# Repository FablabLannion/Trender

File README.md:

# Trender
# Main SW used for Trender Project. See here for details: http://wiki.fablab-lannion.org/index.php?title=Trender

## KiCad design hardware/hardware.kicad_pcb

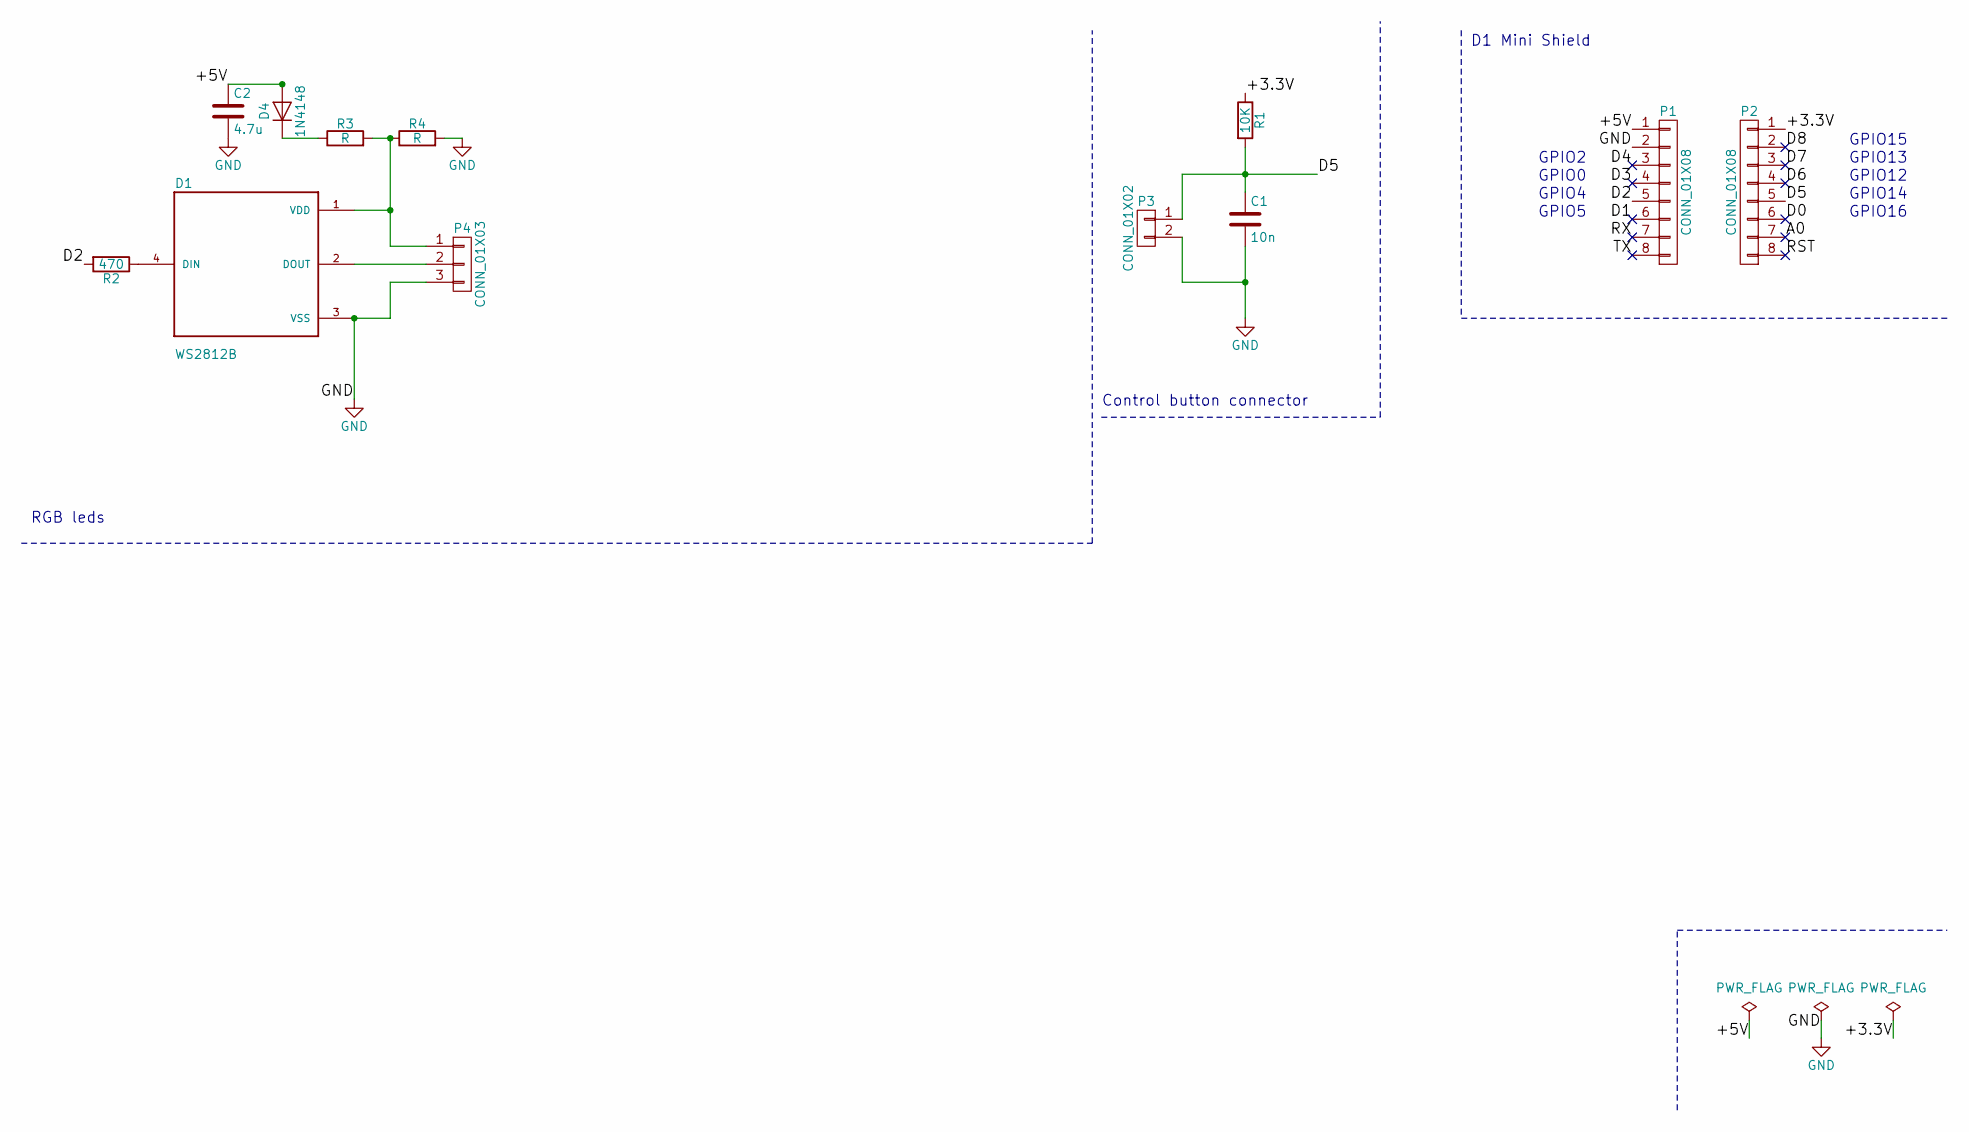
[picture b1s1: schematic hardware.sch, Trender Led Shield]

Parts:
C1: 10n; C_Disc_D3.8mm_W2.6mm_P2.50mm
C2: 4.7u; C_Disc_D3.8mm_W2.6mm_P2.50mm
D1: WS2812B; LED_WS2812B
D4: 1N4148; D_DO-15_P2.54mm_Vertical_KathodeUp
P1, P2: CONN_01X08; D1_mini_Pin_Header
P3: CONN_01X02; Pin_Header_Angled_1x02
P4: CONN_01X03; Pin_Header_Angled_1x03
R1: 10K; R_Axial_DIN0204_L3.6mm_D1.6mm_P2.54mm_Vertical
R2: 470; R_Axial_DIN0204_L3.6mm_D1.6mm_P2.54mm_Vertical
R3, R4: R; R_Axial_DIN0204_L3.6mm_D1.6mm_P2.54mm_Vertical

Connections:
/+3.3V: P2.1, R1.1
/+5V: C2.1, D4.2 (A), P1.1
/A0: P2.7
/D0: P2.6
/D1: P1.6
/D2: P1.5, R2.2
/D3: P1.4
/D4: P1.3
/D5: C1.1, P2.5, P3.1, R1.2
/D6: P2.4
/D7: P2.3
/D8: P2.2
/RST: P2.8
/RX: P1.7
/TX: P1.8
GND: C1.2, C2.2, D1.3 (VSS), P1.2, P3.2, P4.3, R4.2
unnamed: D1.1 (VDD), P4.1, R3.2, R4.1
unnamed: D1.2 (DOUT), P4.2
unnamed: D1.4 (DIN), R2.1
unnamed: D4.1 (K), R3.1

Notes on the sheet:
GPIO2
GPIO0
GPIO4
GPIO5
GPIO15
GPIO13
GPIO12
GPIO14
GPIO16
D1 Mini Shield
RGB leds
Control button connector

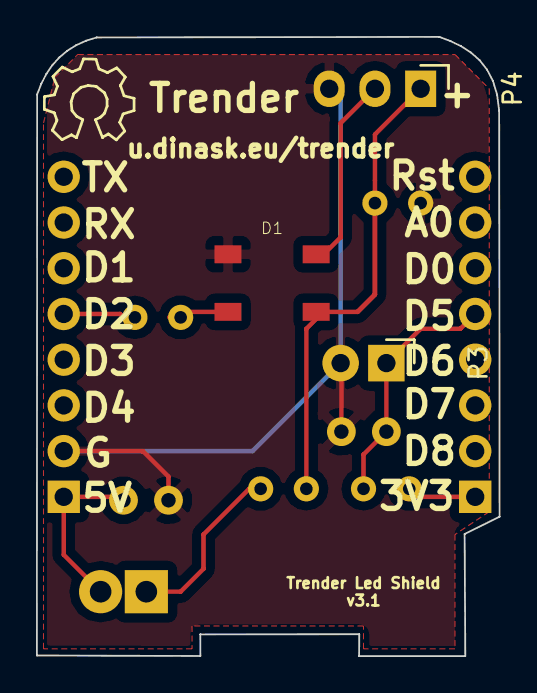
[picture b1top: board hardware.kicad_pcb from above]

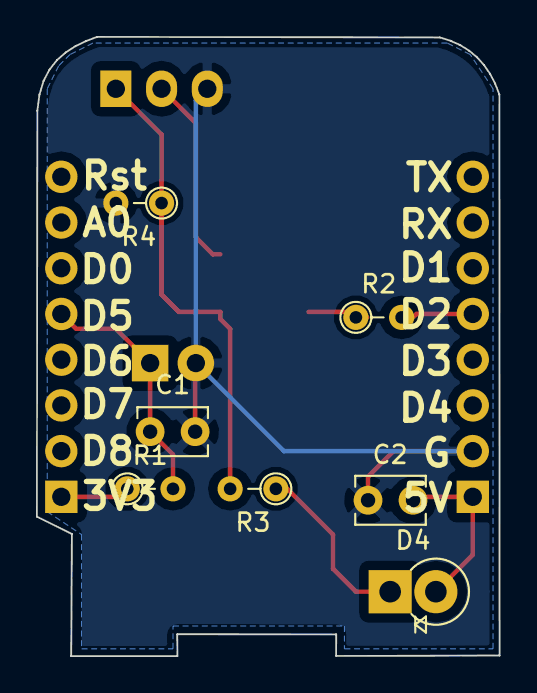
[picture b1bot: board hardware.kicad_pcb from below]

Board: 2 copper layers, 25.7 x 34.4 mm, 12 parts (9 on the bottom side), 9 nets.

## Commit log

2016-03-20 add raspberrypi application and lirc configuration
2016-03-21 Committer: Julien JACQUES <julien.jacques@nokia.com> Changes to be committed: modified: raspberrypi/appli/get_color.sh renamed: raspberrypi/appli/etc/lirc/lircd.conf.gather -> raspberrypi/etc/lirc/li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
2016-03-21 Committer: Julien JACQUES <julien.jacques@nokia.com> Changes to be committed: new file: raspberrypi/appli/cron_color.sh new file: raspberrypi/appli/cube_power_on_off.sh
2016-03-22 Add hardware scheme
2016-03-22 Change email address
2016-06-27 reset branch sweettime
2016-06-27 Init hw scheme
2016-06-27 1s SweetTime v2 version
2016-06-27 Add drawings
2016-06-27 Update doc
2016-06-27 add 1st firmware
2016-06-28 1st re-reading * serial resistor with DIN * decoupling capa for led power * D4 footprint
2016-06-28 1st review : placement/routage
2016-06-28 Move button input to 3.3V
2016-06-28 Update fw to new scheme
2016-06-28 Add connector for led extensions
2016-06-29 Fabrication files
2016-06-29 rename bom
2016-06-29 Add demo sketch * wifi mode AP (ssid: ColorTest, ip:192.168.4.1) * color config web page ** rainbow mode (default) ** "color picker" (3 sliders) * network information web page
2016-06-29 change pinheader face for better 3D display
2016-09-05 config page for Trender
2016-09-06 First functional version of Trender
2016-09-07 Add input "validation"
2016-09-07 1st eeprom store for config
2016-09-07 Correct color write to eeprom
2016-09-07 Correct duration write to eeprom
2016-09-07 Add color fading
2016-09-07 Blink when ready
2016-09-07 add tilt sensor management
2016-10-24 Testing use case
    add Testing use case, used for Adonnantes#3 meeting
2016-10-24 add dedicated headers and comments
2016-12-04 Add Heartbeat checkbox
2016-12-04 Add feature : heartbeat the light can now "pulse" during each color there is 4 levels of pulse speed for each color (the speedest, the less time you have for this color) speed is dependent of color a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
2016-12-04 refine values for heartbeat TKB_BASE_RATE=0.10 brightness steps set to 20 instead of 2
2016-12-04 Add some comments
2016-12-04 Add favicon
2016-12-04 - change heartbeats as follow to be less intrusive: // quarter1: no pulse // quarter2: no pulse // quarter3: one pulse // quarter4: three pulse - setcolor: ensure brightness is set to the maximum by 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
2016-12-04 cleanup following merge issues. Adding comment from commit c588b49f9280f6e727e1abdc12837b0327db6e2c
2016-12-04 Ra-add favicon
2016-12-08 dd version string
2016-12-08 Add GPLv3 licence information
2016-12-11 Add printed piece for stone position
2016-12-13 Add parts of MAC@ at the end of SSID
2016-12-13 Add User Manual
2017-03-19 Ajout .ino et .rld pour les trender jenkins OPNFV
2017-05-01 update Trender OPNFV
2017-05-05 Add captive portal
2017-05-07 remove credentials clean (a little bit)
2017-05-08 extend trender use cases introductin ThingSpeak Connector. AP will be closed after 30s (TK_BASE_TIMEOUT) in case no timekeeper is initiated. ThingSpeak mode can also be forced using dedicated webpage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
2017-05-08 include thingspeak data processing. Following data shall be updated in the code to make it work: const char* channelID = "*****"; char ssid[] = "***"; // your network SSID (name) // TODO : shall be c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
    TODO:
    - wifi connection failure to be enhanced, ESP.restart does not reboot properly, stuck in "wdt reset" mode :-(
    - wifi parameters shall be configurable
    - thingspeak channelid hall be configurable
2017-07-19 first commit for Trender lib
2017-07-19 update readme file
2017-09-13 minor update on Readme.md to test branches
2017-09-13 minor update to check branches
2017-09-13 modify class names : TDR_Sensor to TDR_Device, TDR_Sensor_in to TDR_Sensor and TDS_Sensor_out to TDR_Activator
2017-09-13 modify class names : add TDR_Device and TDR_Activator
2017-09-17 add WifiManager lib to Trender
2017-09-24 add Thingspeak Web connector
2017-09-27 improve Jenkins usage
2017-09-27 add a TDR_mngt field to get back the accesspoint mode (Thingspeak field8=9 then =0)
2017-09-28 add color management from field2,field3,field4 of the ThingSpeak channel
2017-09-28 Update TDR_VERSION to identify the first batch
2017-09-29 enable Timekeeper mode
2017-10-02 prepare pull request
2017-10-05 fix switch to timeKeeperMode within some conditions
2017-10-05 bugfix in thingspeak mode
2017-10-08 bug fix: problem d'include trender.h not found
    ben oui c'est Trender.h, ça semble case sensitive...
2017-10-11 Update Trender_defs.h
    increment TDR_VERSION after the merge from @colvert (commit: 3da637a83233ca64d8f24c24c1e6bec1ffaa0c0b)
2017-10-12 Initiate Trender user guide
2017-10-12 change image path
2017-10-12 add first leaflet svg file
2017-10-12 leaflet source files #1
2017-10-13 Visual update
    Fablab-lannion logo,
    +TM right after "TRENDER"
2017-10-13 remove URL from fablab-lannion logo
2017-12-12 add a push button to TimeKeeper usage
2017-12-13 tweak TimeKeeper with PushButton
2018-02-18 v3.1, refactoring for only one Neopixel
2019-02-10 Upload visuel devfest
2019-02-14 ajout fichier trender devfest
2019-02-19 BugFix : DNS responder for every domain
2019-02-19 Set TimeKeeper as default
